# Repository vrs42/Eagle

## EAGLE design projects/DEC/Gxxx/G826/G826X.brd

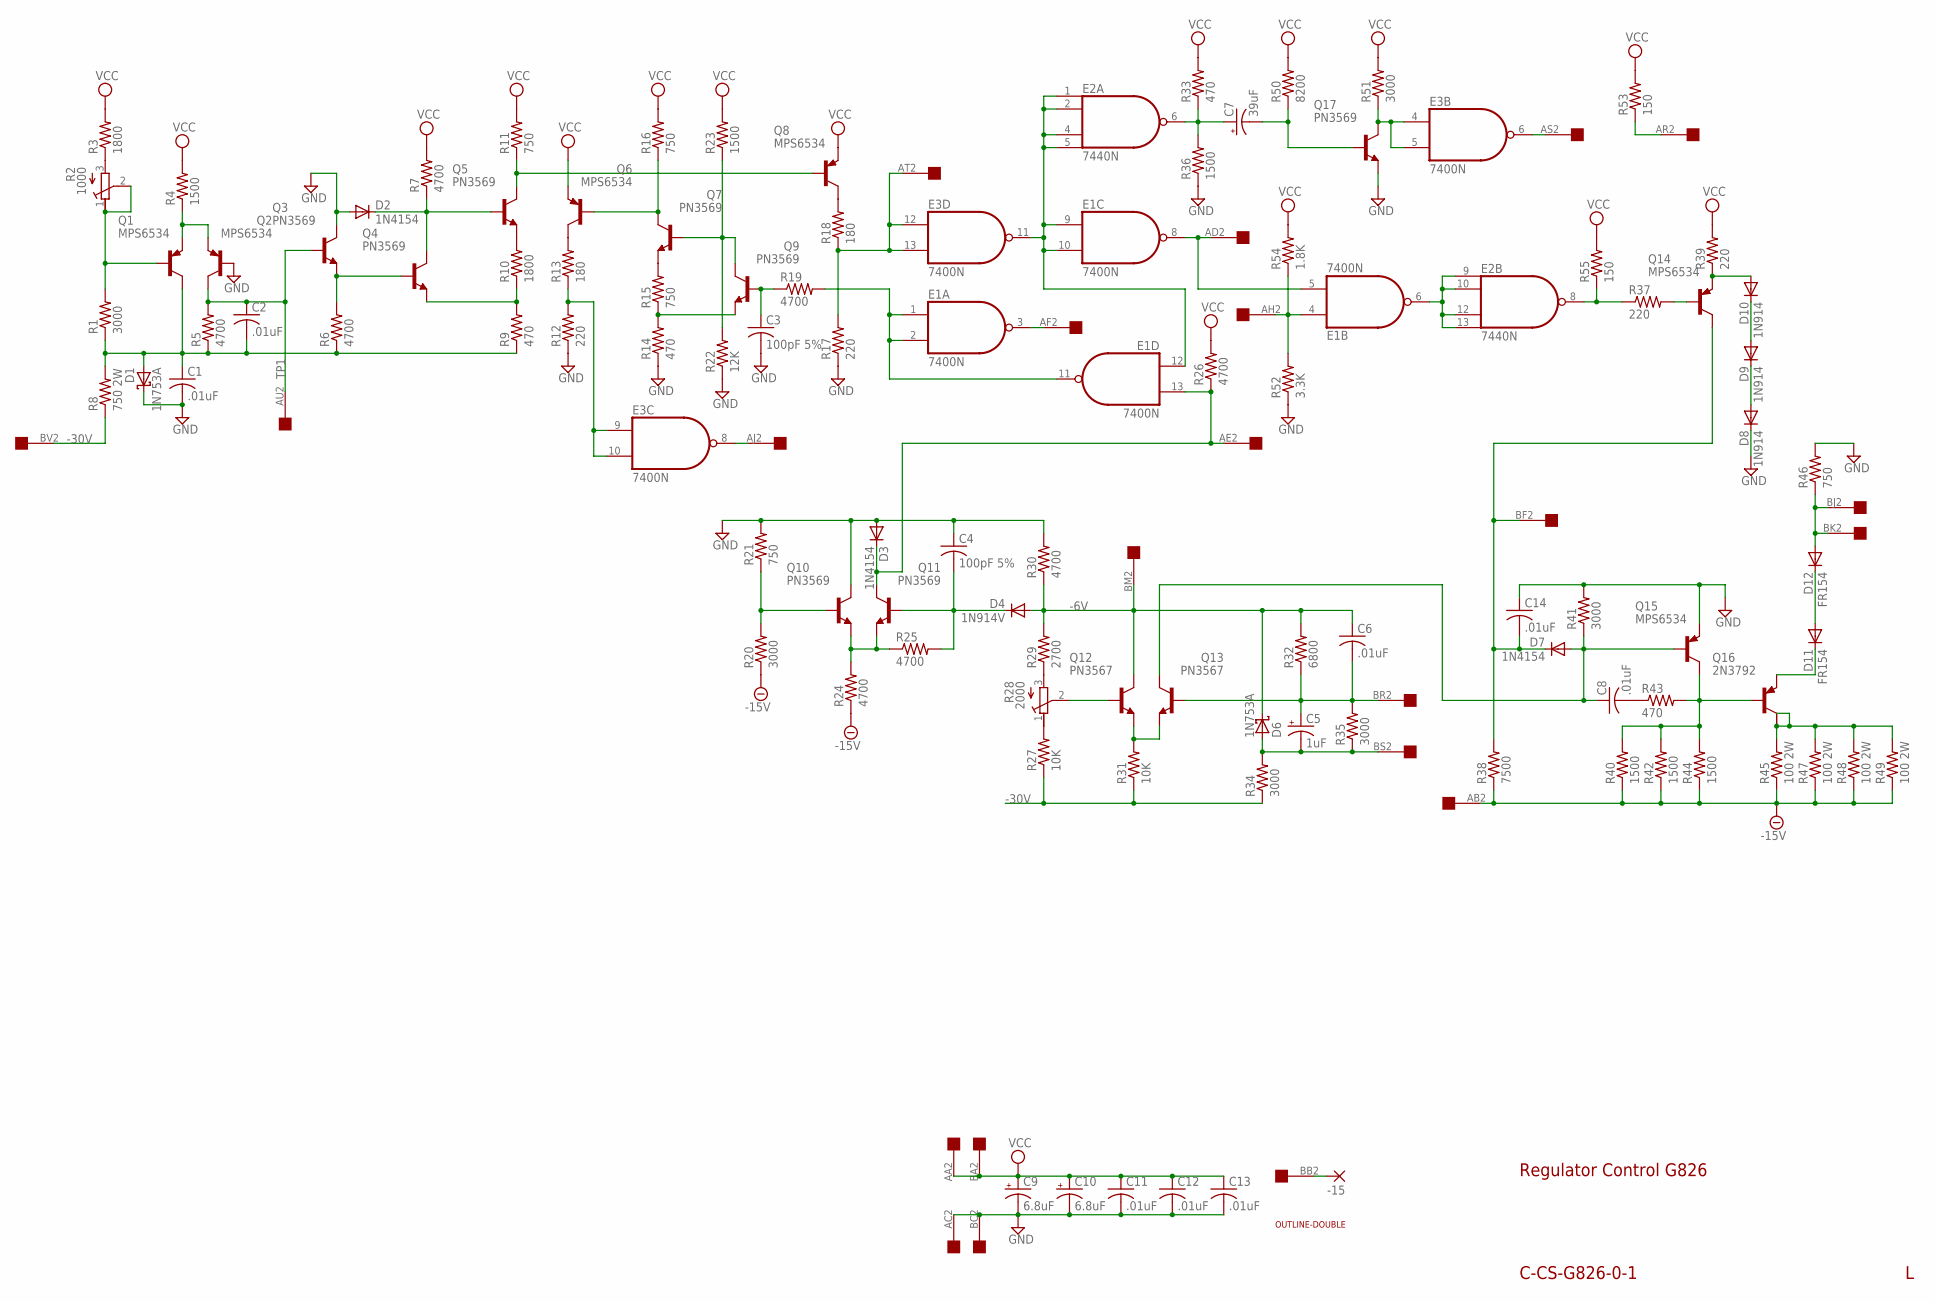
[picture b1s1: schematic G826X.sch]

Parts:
-15: 1,6/0,8
C1, C2, C6, C8, C11, C12, C13, C14: .01uF; C050-025X075
C3, C4: 100pF 5%; C050-025X075
C5: 1uF; E15-5
C7: 39uF; E22-6
C9, C10: 6.8uF; E12-8
D1, D6: 1N753A; DO35-10
D2, D3, D7: 1N4154; DO35-10
D4: 1N914V; DO35-10
D8, D9, D10: 1N914; DO35-10
D11, D12: FR154; DO41-10
E1, E3: 7400N; DIL14
E2: 7440N; DIL14
Q1, Q2, Q6, Q8, Q14, Q15: MPS6534; TO39
Q3, Q4, Q5, Q7, Q9, Q10, Q11, Q17: PN3569; TO5
Q12, Q13: PN3567; TO5
Q16: 2N3792; TO3
R1, R20, R34, R35, R41, R51: 3000; 0207/10
R2: 1000; 3006Y
R3, R10: 1800; 0207/10
R4, R23, R36, R40, R42, R44: 1500; 0207/10
R5, R6, R7, R19, R24, R25, R26, R30: 4700; 0207/10
R8: 750 2W; 0818/25
R9, R14, R33, R43: 470; 0207/10
R11, R15, R16, R21, R46: 750; 0207/10
R12, R17, R37, R39: 220; 0207/10
R13, R18: 180; 0207/10
R22: 12K; 0207/10
R27, R31: 10K; 0207/10
R28: 2000; 3006Y
R29: 2700; 0207/10
R32: 6800; 0207/10
R38: 7500; 0207/10
R45, R47, R48, R49: 100 2W; 0818/25
R50: 8200; 0207/10
R52: 3.3K; 0207/10
R53, R55: 150; 0207/10
R54: 1.8K; 0207/10
U$1: DOUBLE; EDGE-CON4
U$2: OUTLINE-DOUBLE; DOUBLE

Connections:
-6V: C6.1, D4.A, D6.C, Q12.3 (C), R29.2, R30.1, R32.2, U$1.BM2
-15V: R20.1, R24.1, R38.1, R40.1, R42.1, R44.1, R45.1, R47.1, R48.1, R49.1, U$1.AB2
-30V: R8.1, R27.1, R31.1, R34.1, U$1.BV2
GND: C1.2, C3.2, C4.1, C9.-, C10.-, C11.2, C12.2, C13.2, C14.1, D1.C, D2.A, D3.A, D8.C, E1.7 (GND), E2.7 (GND), E3.7 (GND), Q2.2 (B), Q3.3 (C), Q10.3 (C), Q15.1 (E), Q17.1 (E), R12.1, R14.1, R17.1, R21.2, R22.1, R30.2, R36.1, R41.2, R46.2, R52.1, U$1.AC2, U$1.BC2
unnamed: Q1.2 (B), R1.2, R2.1 (A), R2.2 (S)
unnamed: R2.3 (E), R3.1
unnamed: C1.1, C2.2, D1.A, Q1.3 (C), R1.1, R5.1, R6.1, R8.2, R9.1
unnamed: Q1.1 (E), Q2.1 (E), R4.1
unnamed: Q3.1 (E), Q4.2 (B), R6.2
unnamed: Q4.1 (E), R9.2, R10.1
unnamed: D2.C, Q4.3 (C), Q5.2 (B), R7.1
unnamed: Q5.3 (C), Q8.2 (B), R11.1
unnamed: Q5.1 (E), R10.2
unnamed: E3.9 (I0), E3.10 (I1), R12.2, R13.1
unnamed: Q6.3 (C), R13.2
unnamed: E3.8 (O), U$1.AJ2
unnamed: Q6.2 (B), Q7.3 (C), R16.1
unnamed: Q7.1 (E), R15.2
unnamed: Q9.1 (E), R14.2, R15.1
unnamed: Q7.2 (B), Q9.3 (C), R22.2, R23.1
unnamed: Q8.3 (C), R18.2
unnamed: E3.12 (I0), E3.13 (I1), R17.2, R18.1, U$1.AT2
unnamed: E1.9 (I0), E1.10 (I1), E1.12 (I0), E2.1 (I0), E2.2 (I1), E2.4 (I2), E2.5 (I3), E3.11 (O)
unnamed: C3.1, Q9.2 (B), R19.1
unnamed: E1.1 (I0), E1.2 (I1), E1.11 (O), R19.2
unnamed: E1.3 (O), U$1.AF2
unnamed: E1.5 (I1), E1.8 (O), U$1.AD2
unnamed: E1.6 (O), E2.9 (I0), E2.10 (I1), E2.12 (I2), E2.13 (I3)
unnamed: C7.+, E2.6 (O), R33.1, R36.2
unnamed: Q16.C, Q16.C/, R45.2, R47.2, R48.2, R49.2
unnamed: Q15.3 (C), Q16.B, R40.2, R42.2, R43.2, R44.2
unnamed: C7.-, Q17.2 (B), R50.1
unnamed: E3.4 (I0), E3.5 (I1), Q17.3 (C), R51.1
unnamed: E3.6 (O), U$1.AS2
unnamed: E1.4 (I0), R52.2, R54.1, U$1.AH2
unnamed: E2.8 (O), R37.1, R55.1
unnamed: R53.1, U$1.AR2
unnamed: Q14.2 (B), R37.2
unnamed: D10.A, Q14.1 (E), R39.1
unnamed: D8.A, D9.C
unnamed: D9.A, D10.C
unnamed: C14.2, D7.C, Q14.3 (C), R38.2, U$1.BF2
unnamed: -15.1, U$1.BB2
unnamed: Q10.2 (B), R20.2, R21.1
unnamed: Q10.1 (E), Q11.1 (E), R24.2, R25.1
unnamed: D3.C, E1.13 (I1), Q11.3 (C), R26.1, U$1.AE2
unnamed: Q12.2 (B), R28.2 (S)
unnamed: C4.2, D4.C, Q11.2 (B), R25.2
unnamed: Q12.1 (E), Q13.1 (E), R31.2
unnamed: C5.-, D6.A, R34.2, R35.1, U$1.BS2
unnamed: R28.3 (E), R29.1
unnamed: R27.2, R28.1 (A)
unnamed: D11.C, Q16.E
unnamed: C5.+, C6.2, Q13.2 (B), R32.1, R35.2, U$1.BR2
unnamed: C8.1, D7.A, Q13.3 (C), Q15.2 (B), R41.1
unnamed: C8.2, R43.1
unnamed: D11.A, D12.C
unnamed: D12.A, R46.1, U$1.BJ2, U$1.BK2
TP1: C2.1, Q2.3 (C), Q3.2 (B), R5.2, U$1.AU2
VCC: C9.+, C10.+, C11.1, C12.1, C13.1, E1.14 (VCC), E2.14 (VCC), E3.14 (VCC), Q6.1 (E), Q8.1 (E), R3.2, R4.2, R7.2, R11.2, R16.2, R23.2, R26.2, R33.2, R39.2, R50.2, R51.2, R53.2, R54.2, R55.2, U$1.AA2, U$1.BA2

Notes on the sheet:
Regulator Control G826
C-CS-G826-0-1

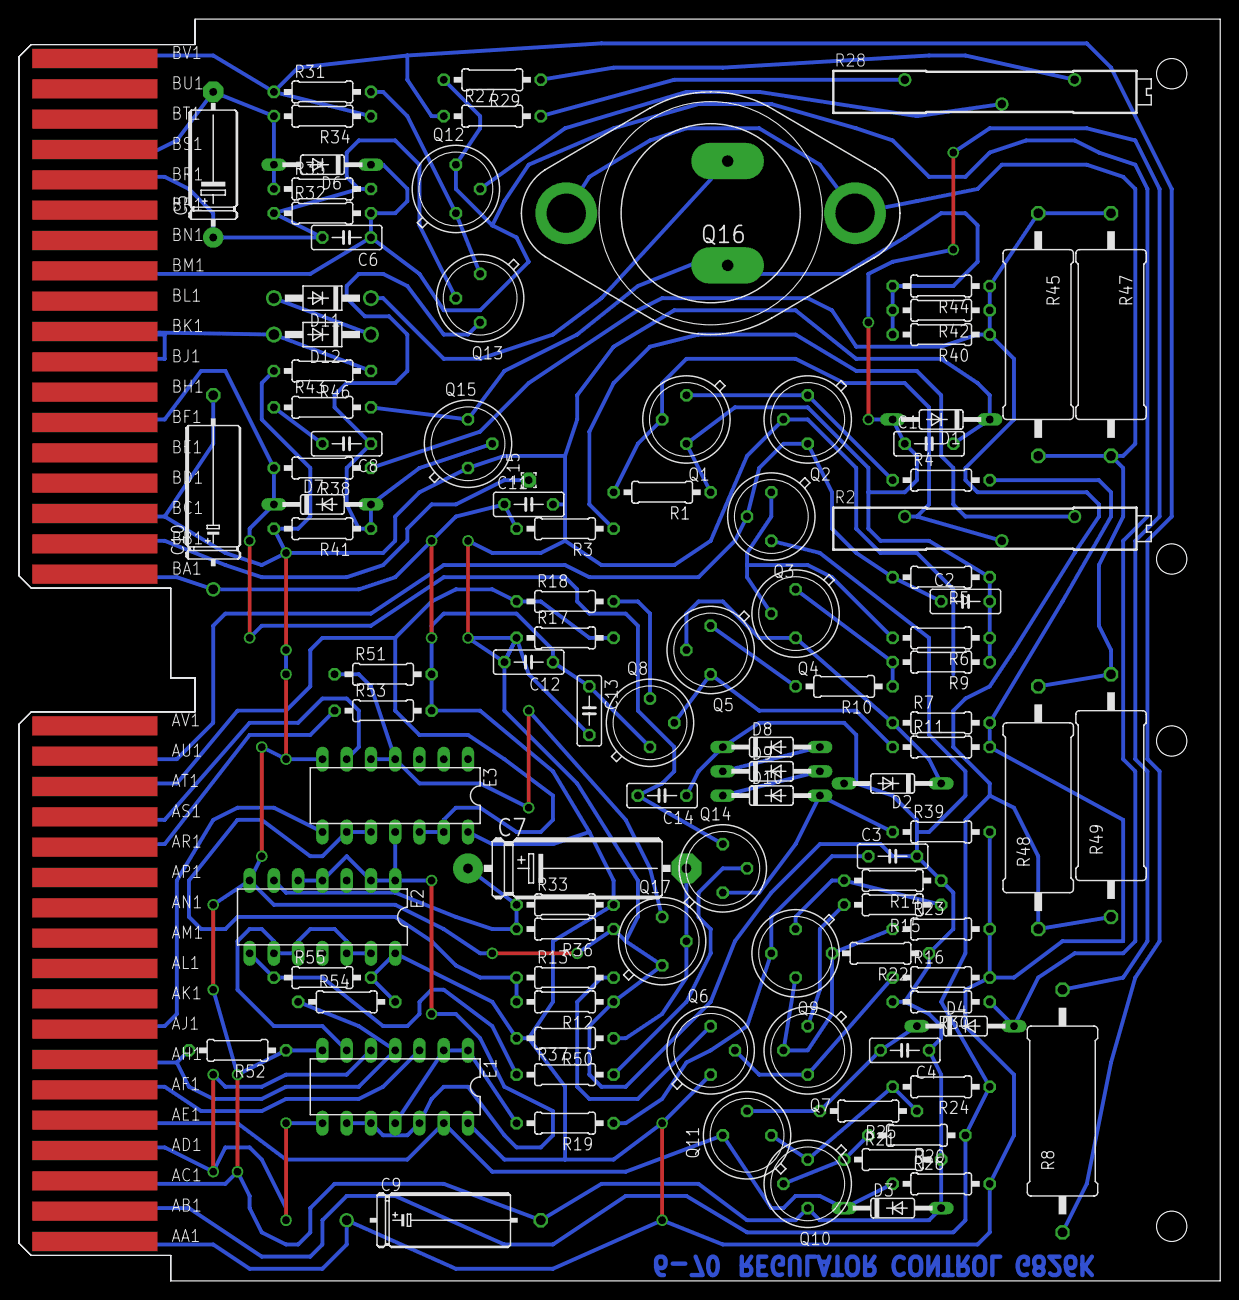
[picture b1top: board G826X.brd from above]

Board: 2 copper layers, 125.7 x 132.1 mm, 103 parts (0 on the bottom side), 60 nets.

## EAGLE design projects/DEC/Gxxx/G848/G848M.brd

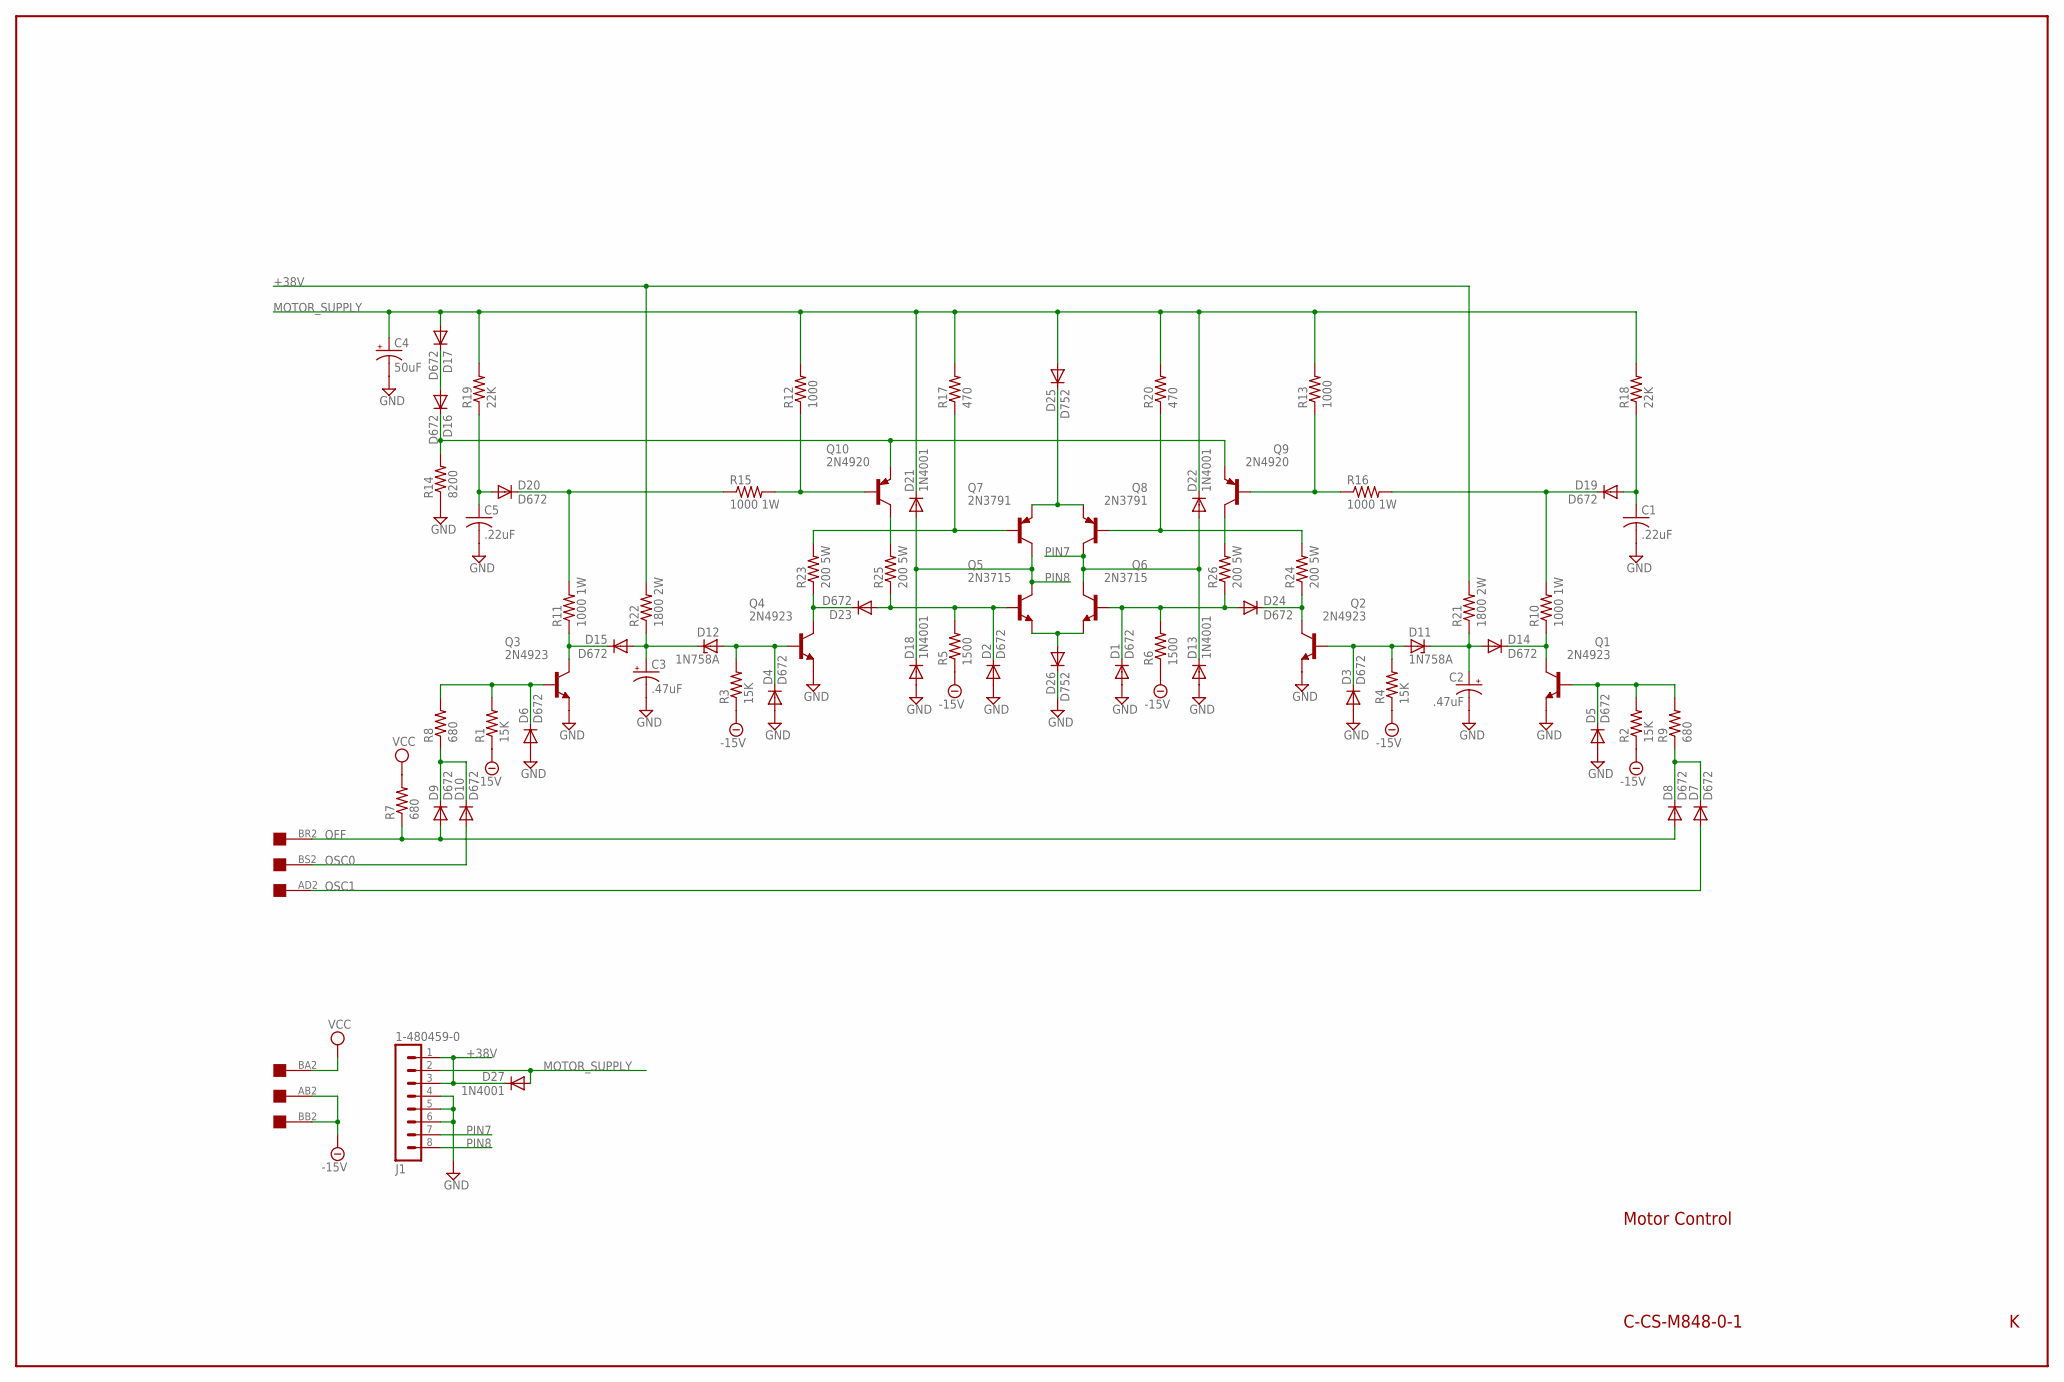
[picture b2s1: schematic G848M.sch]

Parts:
C1, C5: .22uF; C325-137X374
C2, C3: .47uF; E15-5
C4: 50uF; E30-10
D1, D2, D3, D4, D5, D6, D7, D8, D9, D10, D14, D15, D16, D17, D19, D20, D23, D24: D672; DO35-10
D11, D12: 1N758A; DO35Z10
D13, D18, D21, D22, D27: 1N4001; DO41-10
D25, D26: D752; G4-12
J1: 1-480459-0
Q1, Q2, Q3, Q4: 2N4923; TO225AHH
Q5, Q6: 2N3715; TO3
Q7, Q8: 2N3791; TO3
Q9, Q10: 2N4920; TO225AHH
R1, R2, R3, R4: 15K; 0207/10
R5, R6: 1500; 0207/10
R7, R8, R9: 680; 0207/10
R10, R11, R15, R16: 1000 1W; 0414/20
R12, R13: 1000; 0207/10
R14: 8200; 0207/10
R17, R20: 470; 0207/10
R18, R19: 22K; 0207/10
R21, R22: 1800 2W; 0818/25
R23, R24, R25, R26: 200 5W; VTA54
U$1: DOUBLE; EDGE-CON4

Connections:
+38V: D27.C, J1.1, J1.3, R21.2, R22.2
-15V: R1.1, R2.1, R3.1, R4.1, R5.1, R6.1, U$1.AB2, U$1.BB2
GND: C1.2, C2.-, C3.-, C4.-, C5.2, D1.A, D2.A, D3.A, D4.A, D5.A, D6.A, D13.A, D18.A, D26.C, J1.4, J1.5, J1.6, Q1.1 (E), Q2.1 (E), Q3.1 (E), Q4.1 (E), R14.1
MOTOR_SUPPLY: C4.+, D17.A, D21.C, D22.C, D25.A, D27.A, J1.2, R12.2, R13.2, R17.2, R18.2, R19.2, R20.2
unnamed: D9.C, D10.C, R8.1
unnamed: D16.C, Q9.1 (E), Q10.1 (E), R14.2
unnamed: D16.A, D17.C
unnamed: C5.1, D20.A, R19.1
unnamed: D15.C, Q3.2 (C), R11.1
unnamed: C3.+, D12.C, D15.A, R22.1
unnamed: D20.C, R11.2, R15.1
unnamed: D6.C, Q3.3 (B), R1.2, R8.2
unnamed: D4.C, D12.A, Q4.3 (B), R3.2
unnamed: Q10.2 (C), R25.2
unnamed: D23.C, Q4.2 (C), R23.1
unnamed: Q7.B, R17.1, R23.2
unnamed: D2.C, D23.A, Q5.B, R5.2, R25.1
unnamed: Q10.3 (B), R12.1, R15.2
unnamed: D1.C, D24.A, Q6.B, R6.2, R26.1
unnamed: D26.A, Q5.E, Q6.E
unnamed: D25.C, Q7.E, Q8.E
unnamed: Q8.B, R20.1, R24.2
unnamed: Q9.2 (C), R26.2
unnamed: D24.C, Q2.2 (C), R24.1
unnamed: Q9.3 (B), R13.1, R16.1
unnamed: D3.C, D11.A, Q2.3 (B), R4.2
unnamed: C2.+, D11.C, D14.A, R21.1
unnamed: D14.C, Q1.2 (C), R10.1
unnamed: D5.C, Q1.3 (B), R2.2, R9.2
unnamed: D7.C, D8.C, R9.1
unnamed: D19.C, R10.2, R16.2
unnamed: C1.1, D19.A, R18.1
OFF: D8.A, D9.A, R7.1, U$1.BR2
OSC0: D10.A, U$1.BS2
OSC1: D7.A, U$1.AD2
PIN7: D13.C, D22.A, J1.7, Q6.C, Q6.C/ (C), Q8.C, Q8.C/ (C)
PIN8: D18.C, D21.A, J1.8, Q5.C, Q5.C/ (C), Q7.C, Q7.C/ (C)
VCC: R7.2, U$1.BA2

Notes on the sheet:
Motor Control
C-CS-M848-0-1

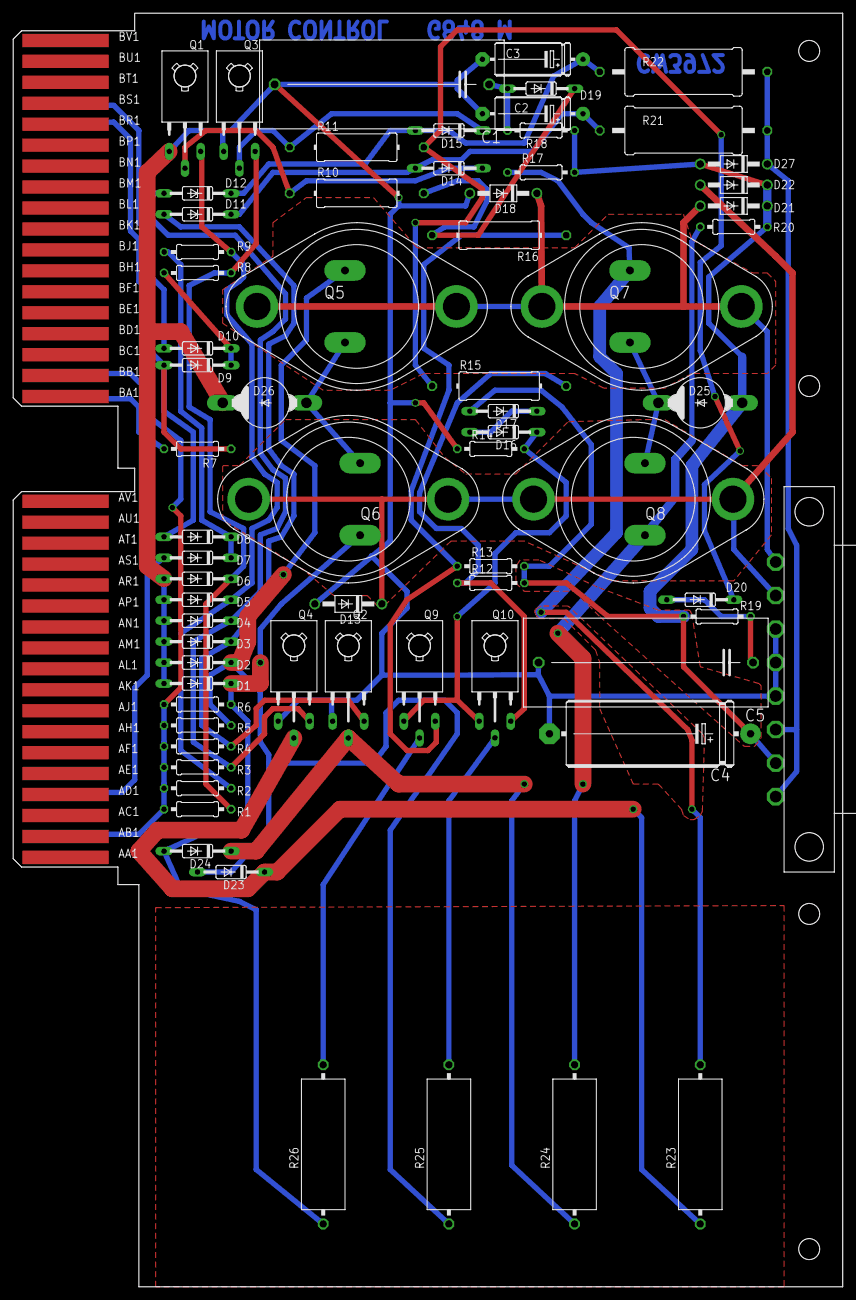
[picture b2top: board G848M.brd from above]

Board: 2 copper layers, 125.7 x 193.0 mm, 70 parts (0 on the bottom side), 38 nets.

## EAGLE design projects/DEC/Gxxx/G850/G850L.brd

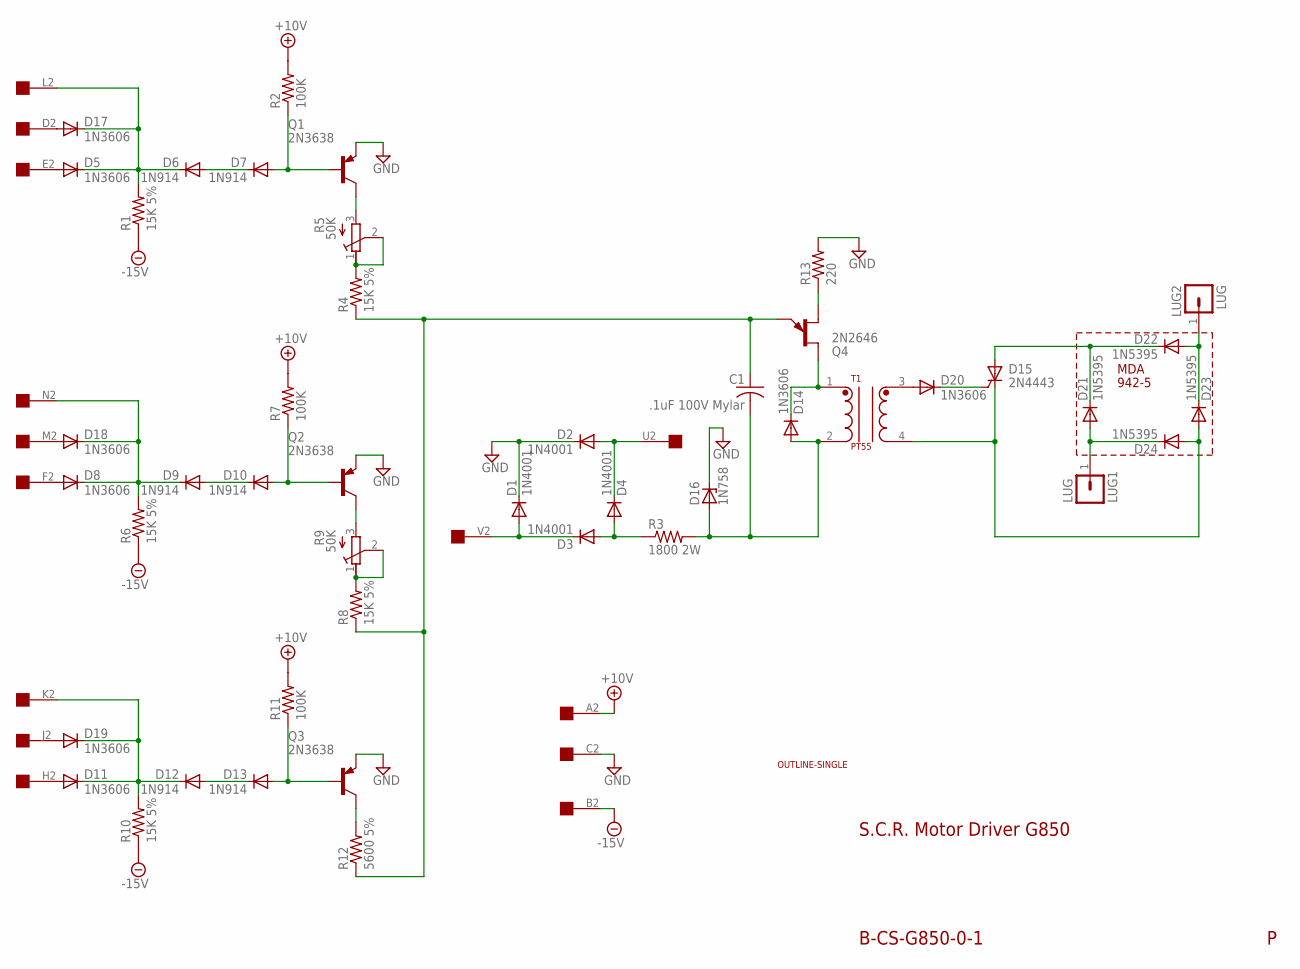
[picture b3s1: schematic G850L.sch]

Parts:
C1: .1uF 100V Mylar; C275-093X316
D1, D2, D3, D4: 1N4001; DO41-10
D5, D8, D11, D14, D17, D18, D19, D20: 1N3606; DO35-10
D6, D7, D9, D10, D12, D13: 1N914; DO35-10
D15: 2N4443; TO220CL
D16: 1N758; DO35Z10
D21, D22, D23, D24: 1N5395; DO41-10
LUG1, LUG2: LUG; SPADELUG
Q1, Q2, Q3: 2N3638; TO39
Q4: 2N2646; TO72I
R1, R4, R6, R8, R10: 15K 5%; 0207/10
R2, R7, R11: 100K; 0207/10
R3: 1800 2W; P0817/22
R5, R9: 50K; 3006Y
R12: 5600 5%; 0207/10
R13: 220; 0207/10
T1: PT55
U$1: OUTLINE-SINGLE; SINGLE
U$2: EDGE-1; EDGE-CON1

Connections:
+10V: R2.2, R7.2, R11.2, U$2.A2
-15V: R1.1, R6.1, R10.1, U$2.B2
GND: D1.C, D2.C, D16.C, Q1.1 (E), Q2.1 (E), Q3.1 (E), R13.2, U$2.C2
unnamed: D17.A, U$2.D2
unnamed: D5.A, U$2.E2
unnamed: D5.C, D6.C, D17.C, R1.2, U$2.L2
unnamed: R4.2, R5.1 (A), R5.2 (S)
unnamed: D9.A, D10.C
unnamed: Q2.3 (C), R9.3 (E)
unnamed: D10.A, Q2.2 (B), R7.1
unnamed: D8.C, D9.C, D18.C, R6.2, U$2.N2
unnamed: R8.2, R9.1 (A), R9.2 (S)
unnamed: D12.A, D13.C
unnamed: Q3.3 (C), R12.2
unnamed: D13.A, Q3.2 (B), R11.1
unnamed: D11.C, D12.C, D19.C, R10.2, U$2.K2
unnamed: Q1.3 (C), R5.3 (E)
unnamed: D18.A, U$2.M2
unnamed: D8.A, U$2.F2
unnamed: D19.A, U$2.J2
unnamed: D11.A, U$2.H2
unnamed: C1.1, Q4.E, R4.1, R8.1, R12.1
unnamed: Q4.B1, R13.1
unnamed: D7.A, Q1.2 (B), R2.1
unnamed: C1.2, D14.A, D16.A, R3.2, T1.2
unnamed: D15.C, D23.A, D24.A, T1.4
unnamed: D3.A, D4.A, R3.1
unnamed: D2.A, D4.C, U$2.U2
unnamed: D1.A, D3.C, U$2.V2
unnamed: D22.A, D23.C, LUG2.1
unnamed: D21.A, D24.C, LUG1.1
unnamed: D6.A, D7.C
unnamed: D15.A, D21.C, D22.C
unnamed: D15.G, D20.C
unnamed: D14.C, Q4.B2, T1.1
unnamed: D20.A, T1.3

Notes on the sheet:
S.C.R. Motor Driver G850
B-CS-G850-0-1
MDA
942-5

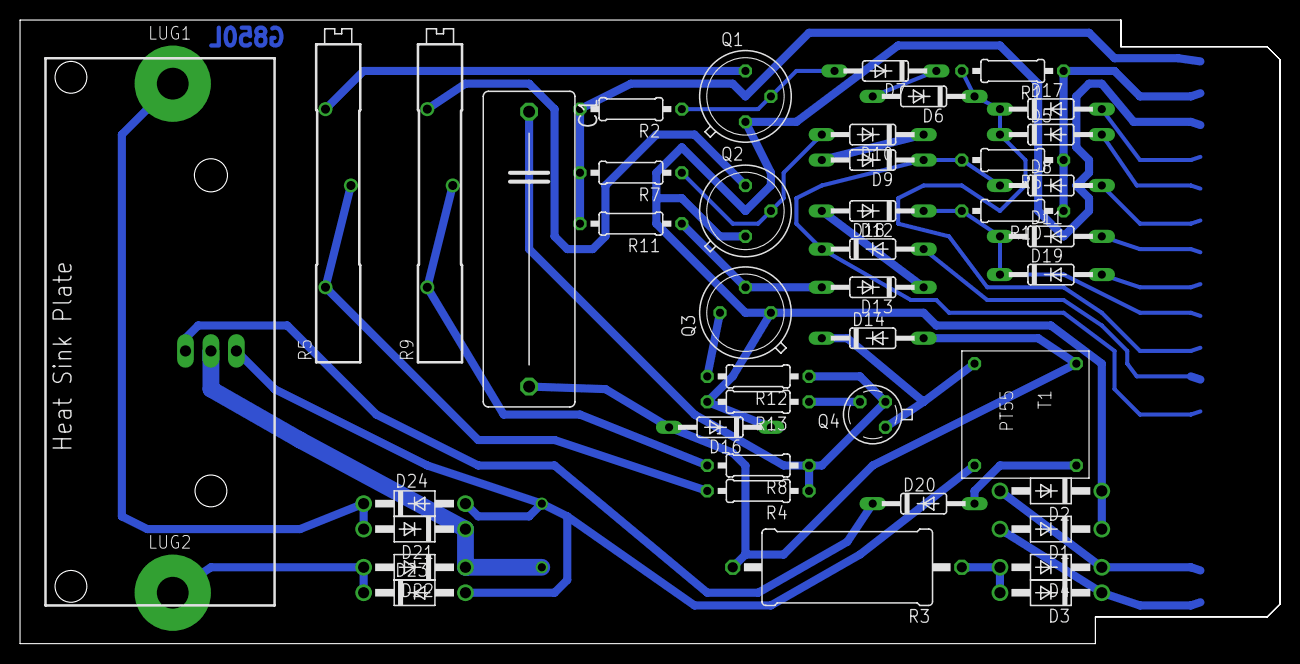
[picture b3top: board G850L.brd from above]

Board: 2 copper layers, 125.7 x 62.2 mm, 47 parts (1 on the bottom side), 36 nets.

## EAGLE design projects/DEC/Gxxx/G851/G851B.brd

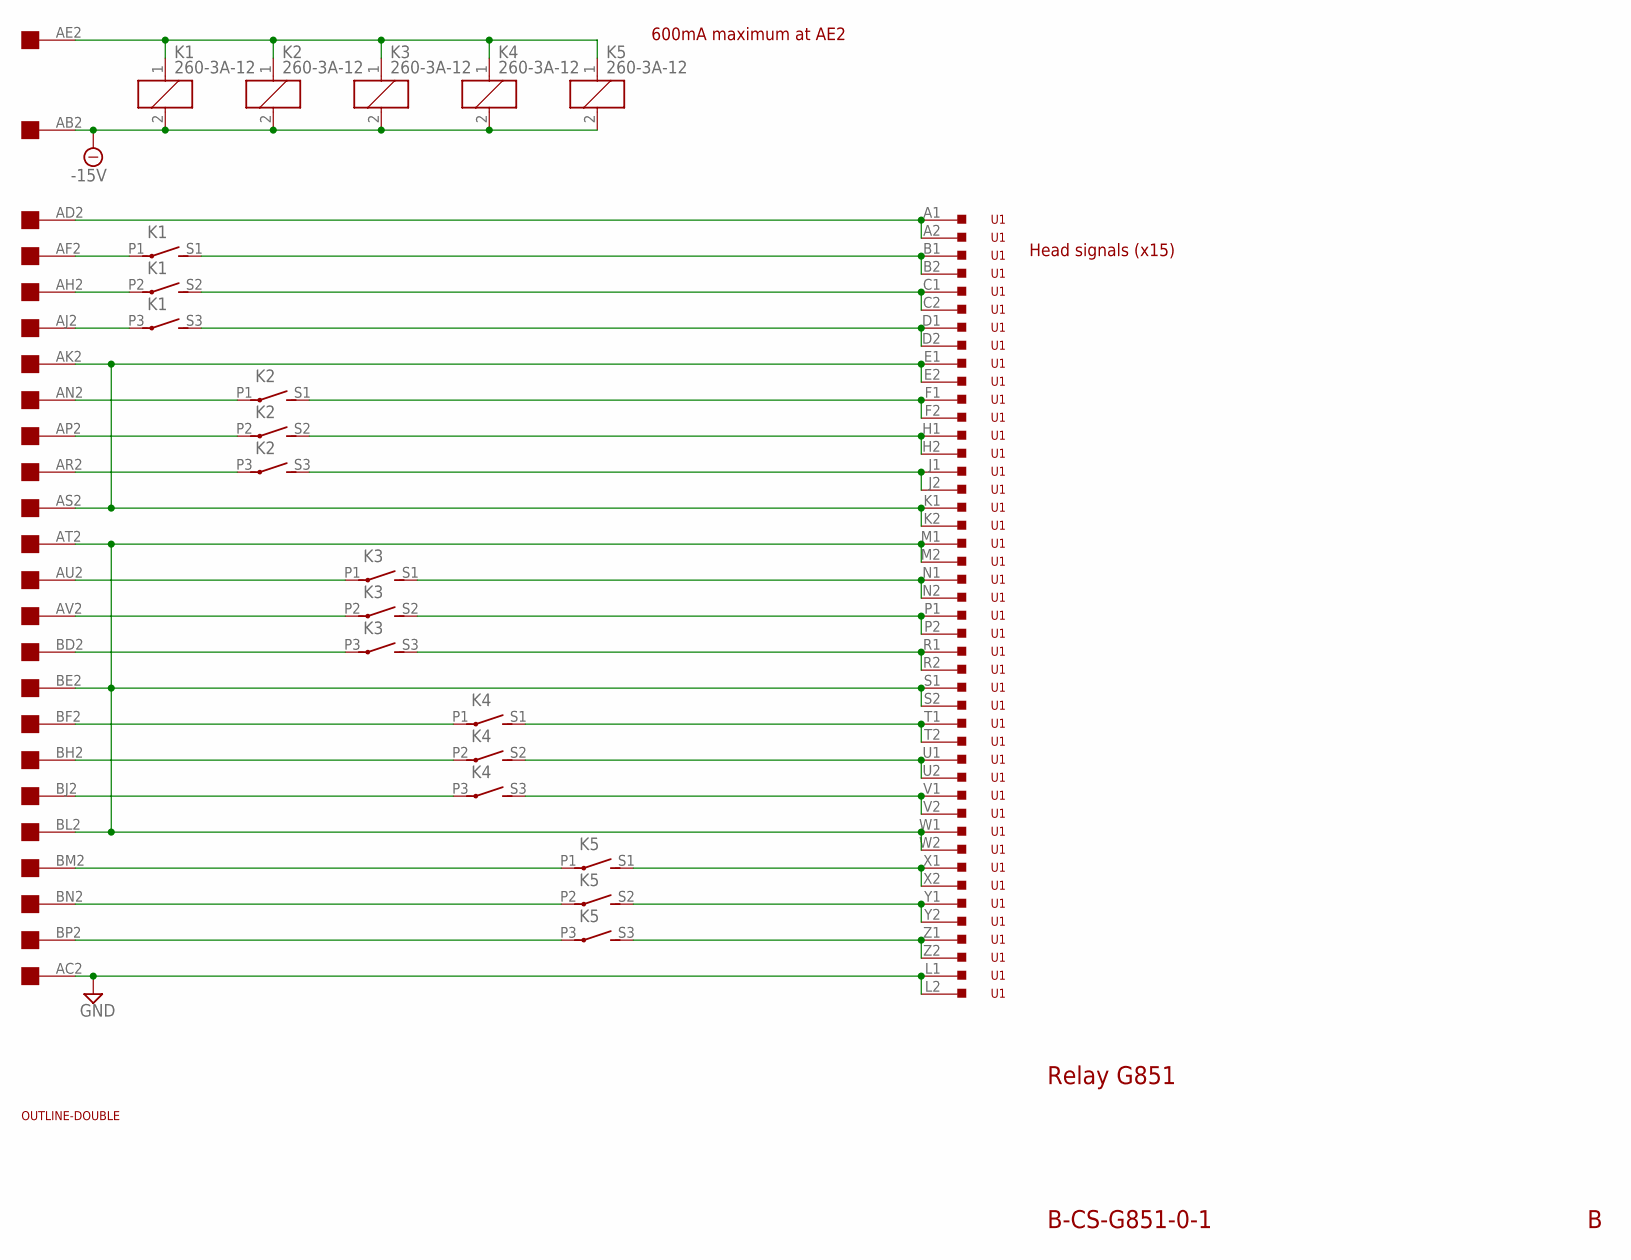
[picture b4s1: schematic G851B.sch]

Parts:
K1, K2, K3, K4, K5: 260-3A-12
U1: 133-022-03
U$1: DOUBLE; EDGE-CON4
U$3: OUTLINE-DOUBLE; DOUBLE

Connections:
-15V: K1.2, K2.2, K3.2, K4.2, K5.2, U$1.AB2
GND: U1.L1, U1.L2, U$1.AC2
unnamed: U1.A1, U1.A2, U$1.AD2
unnamed: K1.P1, U$1.AF2
unnamed: K1.P2, U$1.AH2
unnamed: K1.P3, U$1.AJ2
unnamed: K2.P1, U$1.AN2
unnamed: K2.P2, U$1.AP2
unnamed: K2.P3, U$1.AR2
unnamed: U1.E1, U1.E2, U1.K1, U1.K2, U$1.AK2, U$1.AS2
unnamed: U1.M1, U1.M2, U1.S1, U1.S2, U1.W1, U1.W2, U$1.AT2, U$1.BE2, U$1.BL2
unnamed: K5.P1, U$1.BM2
unnamed: K5.P2, U$1.BN2
unnamed: K5.P3, U$1.BP2
unnamed: K4.P3, U$1.BJ2
unnamed: K4.P2, U$1.BH2
unnamed: K4.P1, U$1.BF2
unnamed: K3.P3, U$1.BD2
unnamed: K3.P2, U$1.AV2
unnamed: K3.P1, U$1.AU2
unnamed: K1.1, K2.1, K3.1, K4.1, K5.1, U$1.AE2
unnamed: K1.S3 (S), U1.D1, U1.D2
unnamed: K1.S2 (S), U1.C1, U1.C2
unnamed: K1.S1 (S), U1.B1, U1.B2
unnamed: K5.S2 (S), U1.Y1, U1.Y2
unnamed: K2.S1 (S), U1.F1, U1.F2
unnamed: K2.S2 (S), U1.H1, U1.H2
unnamed: K2.S3 (S), U1.J1, U1.J2
unnamed: K3.S1 (S), U1.N1, U1.N2
unnamed: K3.S2 (S), U1.P1, U1.P2
unnamed: K3.S3 (S), U1.R1, U1.R2
unnamed: K4.S1 (S), U1.T1, U1.T2
unnamed: K4.S2 (S), U1.U1, U1.U2
unnamed: K4.S3 (S), U1.V1, U1.V2
unnamed: K5.S1 (S), U1.X1, U1.X2
unnamed: K5.S3 (S), U1.Z1, U1.Z2

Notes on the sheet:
Relay G851
B-CS-G851-0-1
600mA maximum at AE2
Head signals (x15)

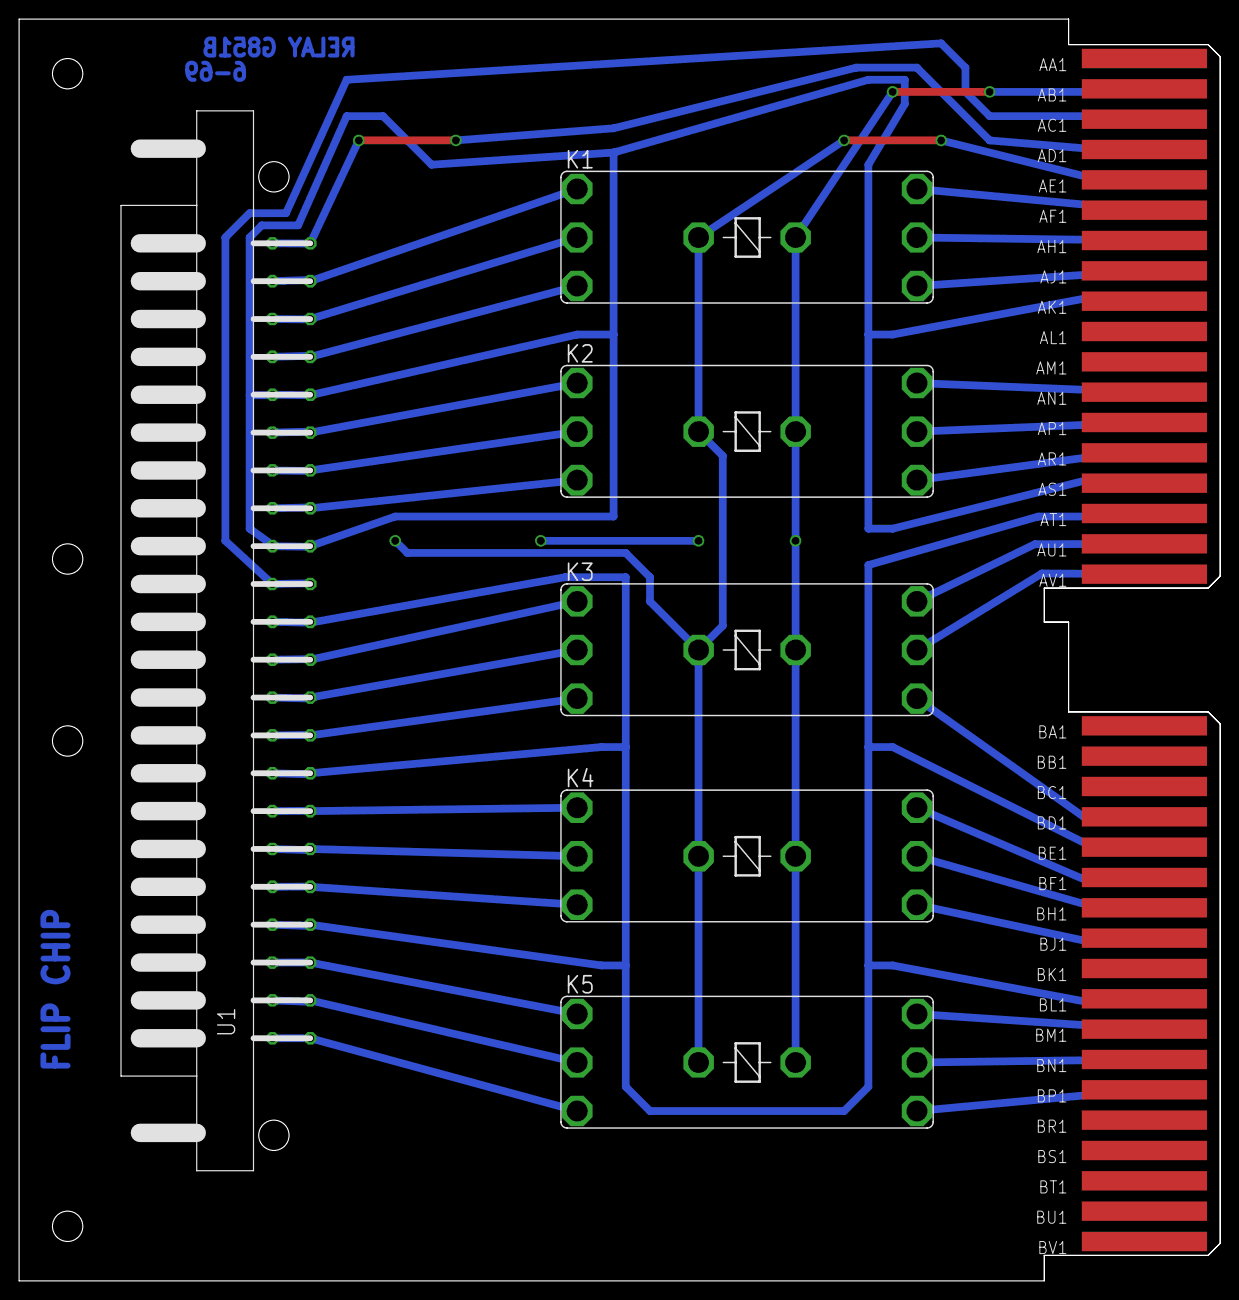
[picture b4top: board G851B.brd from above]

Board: 2 copper layers, 125.7 x 132.1 mm, 8 parts (0 on the bottom side), 36 nets.
